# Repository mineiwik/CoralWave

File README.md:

# CoralWave

This repository contains the hardware design files for an RF transceiver system built using an ESP32-C3 module and a CC1101 RF chip. The communication between the ESP32-C3 and CC1101 is established through the Serial Peripheral Interface (SPI) protocol. The design is created using KiCad 7.

## Abstract

The project aims to create a versatile RF communication system by integrating the ESP32-C3 module and the CC1101 RF chip. The ESP32-C3 serves as the main controller, handling data processing and interfacing with external devices, while the CC1101 handles the RF communication with other compatible devices. This design allows for bi-directional communication over a designated RF frequency band, making it suitable for various applications such as replacing remote controls.

**Note:** The design around the CC1101 chip is tuned for the 315/433 MHz ISM/SRD frequency bands. (See the documentation of the [CC1101](https://www.ti.com/lit/ds/symlink/cc1101.pdf) chip for more information.)

## Opening the Design

Follow these steps to open the hardware design using KiCad 7:

1. Clone this repository to your local machine using the following command:

   ```
   git clone https://github.com/mineiwik/CoralWave.git
   ```

2. Launch KiCad 7.

3. Open the KiCad project by navigating to the project directory and locating the `.kicad_pro` file. This file stores the project information.

4. Once the project is open, you can access the schematic and PCB layout files by clicking on the respective buttons in the KiCad project manager.

5. Adjust the design and/or export the gerbel files for PCB production

## Design Files

The repository contains the following design files:

- Schematic files (`.kicad_sch`) - These files define the circuit connections and component values.
- PCB layout files (`.kicad_pcb`) - These files represent the physical arrangement of components on the PCB.
- Component libraries (see the `PCBLib` submodule) - Custom libraries that include footprints and symbols for the ESP32-C3, CC1101, and other components used in the design.

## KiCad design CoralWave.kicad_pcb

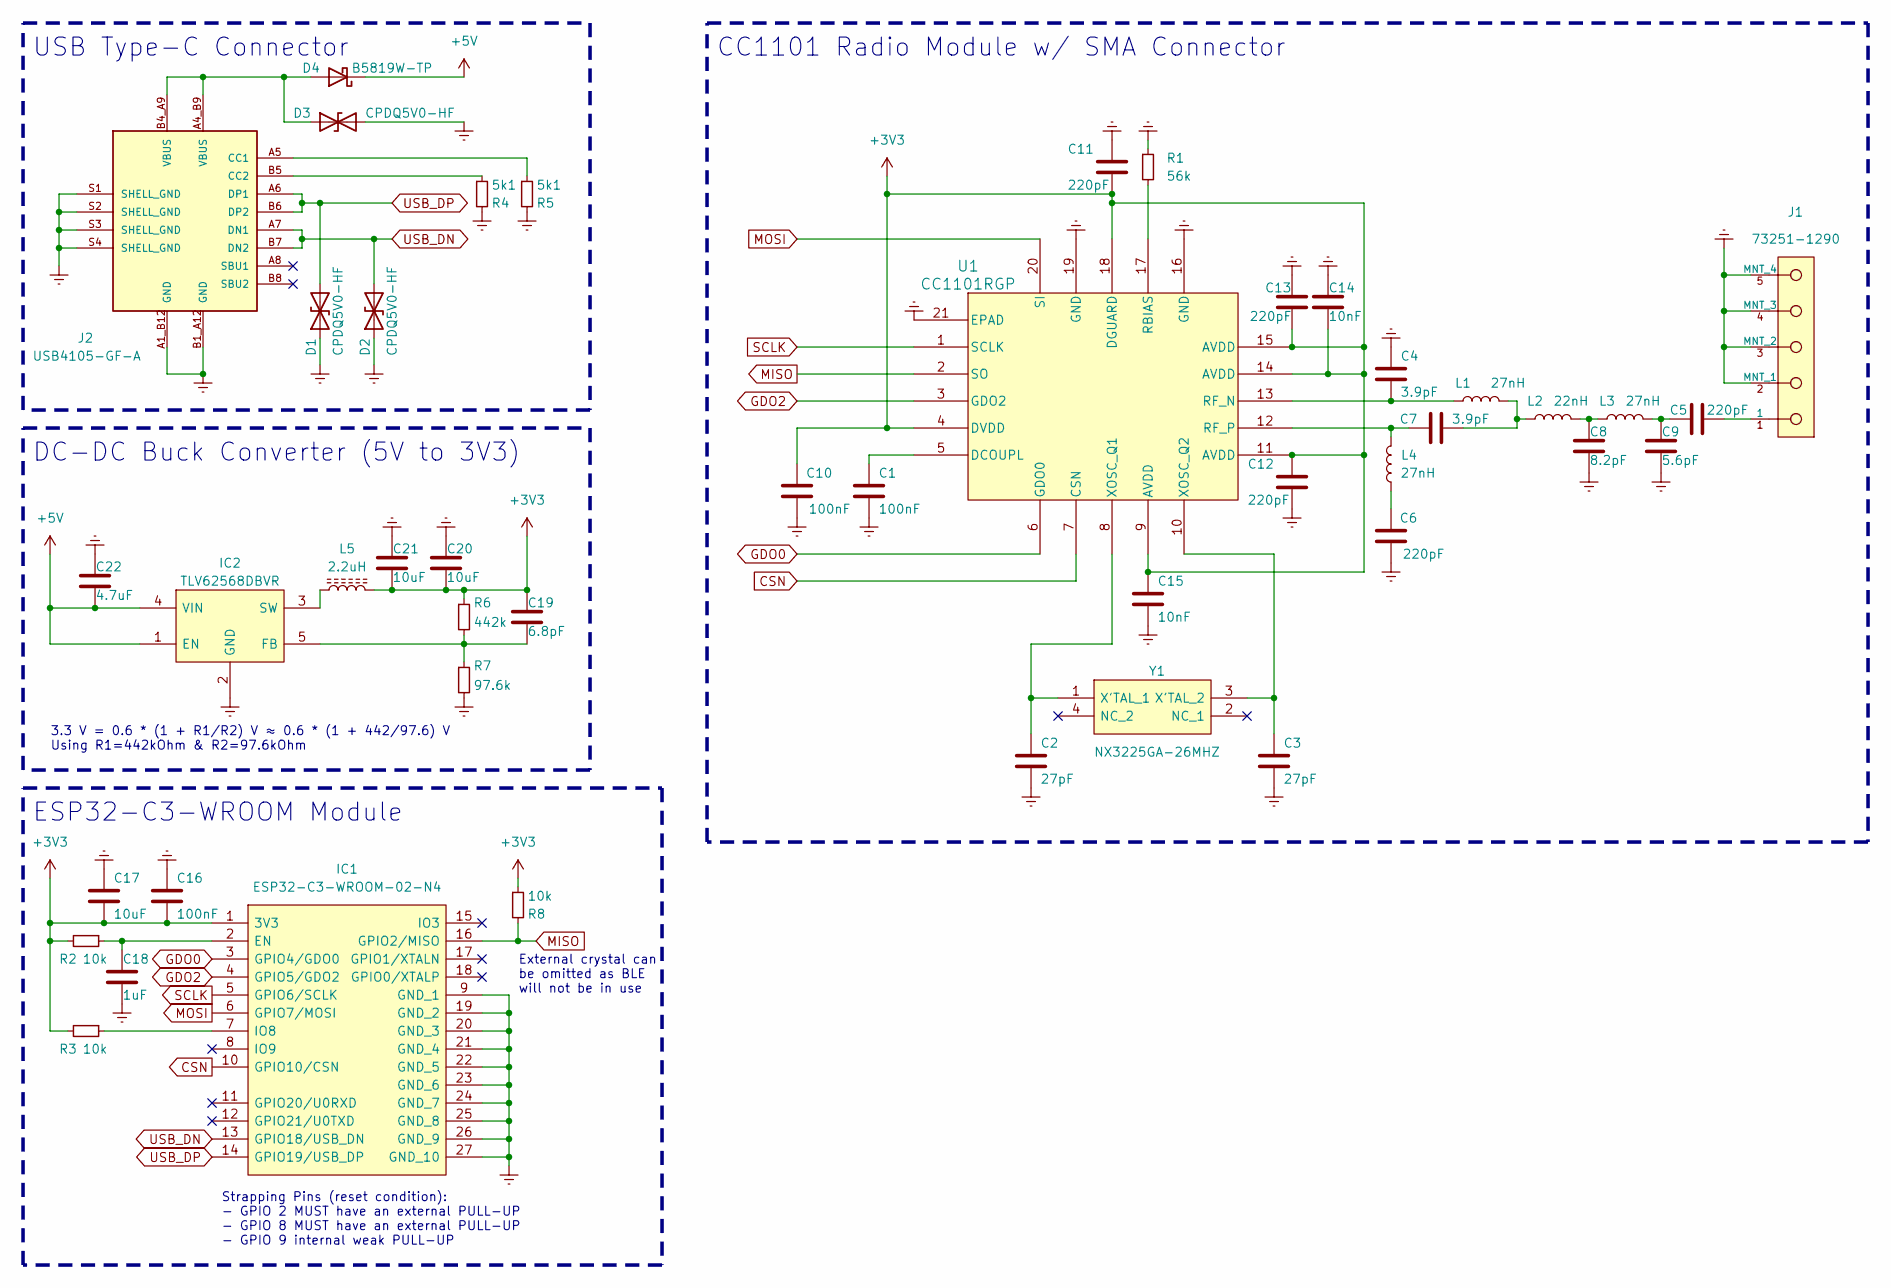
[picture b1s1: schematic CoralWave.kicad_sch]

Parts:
C1, C10, C16: 100nF; Cap_Murata_GRM_0402
C2, C3: 27pF; Cap_Murata_GRM_0402
C4, C7: 3.9pF; Cap_Murata_GRM_0402
C5, C6, C11, C12, C13: 220pF; Cap_Murata_GRM_0402
C8: 8.2pF; Cap_Murata_GRM_0402
C9: 5.6pF; Cap_Murata_GRM_0402
C14, C15: 10nF; Cap_Murata_GRM_0402
C17, C20, C21: 10uF; Cap_Murata_GRM_0402
C18: 1uF; Cap_Murata_GRM_0402
C19: 6.8pF; Cap_Murata_GRM_0402
C22: 4.7uF; Cap_Murata_GRM_0603
D1, D2, D3: CPDQ5V0-HF; SODFL1006X40N
D4: B5819W-TP; SOD3716X135N
IC1: ESP32-C3-WROOM-02-N4; ESP32C3WROOM02N4; Mouser Part Number 356-ESP32C3WROOM02N4
IC2: TLV62568DBVR; Mouser Part Number 595-TLV62568DBVR
J1: 73251-1290; Molex-SD-73251-129; mouser part number 538-73251-1290; digikey description SMA Connector Jack, Female Socket 50 Oh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
J2: USB4105-GF-A; GCT_USB4105-GF-A; PARTREV A3
L1, L3, L4: 27nH; L_Murata_LQG_0402
L2: 22nH; L_Murata_LQG_0402
L5: 2.2uH; ASPI0418FS
R1: 56k; R_KOA_RK_0402
R2, R3, R8: 10k; R_Vishay_CRCW_0402
R4, R5: 5k1; R_Vishay_CRCW_0402
R6: 442k; R_Bourns_CR_0603
R7: 97.6k; R_Bourns_CR_0603
U1: CC1101RGP
Y1: NX3225GA-26MHZ; NX3225GA16000MSTDCRG1; Mouser Part Number 344-NX3225GA26MHZEXS

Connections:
+3V3: C10.2, C11.2, C12.1, C13.2, C14.2, C15.1, C16.2, C17.2, C19.2, C20.2, C21.2, IC1.1 (3V3), L5.2, R2.2, R3.2, R6.1, R8.1, U1.4 (DVDD), U1.9 (AVDD), U1.11 (AVDD), U1.14 (AVDD), U1.15 (AVDD), U1.18 (DGUARD)
+5V: C22.1, D4.1 (K), IC2.1 (EN), IC2.4 (VIN)
CSN: IC1.10 (GPIO10/CSN), U1.7 (CSN)
Earth: C1.2, C2.2, C3.2, C4.1, C6.1, C8.1, C9.1, C10.1, C11.1, C12.2, C13.1, C14.1, C15.2, C16.1, C17.1, C18.2, C20.1, C21.1, C22.2, D1.1 (A1), D2.1 (A1), D3.2 (A2), IC1.9 (GND_1), IC1.19 (GND_2), IC1.20 (GND_3), IC1.21 (GND_4), IC1.22 (GND_5), IC1.23 (GND_6), IC1.24 (GND_7), IC1.25 (GND_8), IC1.26 (GND_9), IC1.27 (GND_10), IC2.2 (GND), J1.2 (MNT_1), J1.3 (MNT_2), J1.4 (MNT_3), J1.5 (MNT_4), J2.A1_B12 (GND), J2.B1_A12 (GND), J2.S1 (SHELL_GND), J2.S2 (SHELL_GND), J2.S3 (SHELL_GND), J2.S4 (SHELL_GND), R1.1, R4.2, R5.2, R7.2, U1.16 (GND), U1.19 (GND), U1.21 (EPAD)
GDO0: IC1.3 (GPIO4/GDO0), U1.6 (GDO0)
GDO2: IC1.4 (GPIO5/GDO2), U1.3 (GDO2)
MISO: IC1.16 (GPIO2/MISO), R8.2, U1.2 (SO)
MOSI: IC1.6 (GPIO7/MOSI), U1.20 (SI)
unnamed: C5.1, C9.2, L3.2
unnamed: C5.2, J1.1
unnamed: C6.2, L4.1
unnamed: C7.2, L1.2, L2.1
unnamed: C8.2, L2.2, L3.1
unnamed: D3.1 (A1), D4.2 (A), J2.A4_B9 (VBUS), J2.B4_A9 (VBUS)
unnamed: C18.1, IC1.2 (EN), R2.1
unnamed: IC1.7 (IO8), R3.1
unnamed: C19.1, IC2.5 (FB), R6.2, R7.1
unnamed: IC2.3 (SW), L5.1
unnamed: J2.A5 (CC1), R5.1
unnamed: J2.B5 (CC2), R4.1
unnamed: C1.1, U1.5 (DCOUPL)
unnamed: R1.2, U1.17 (RBIAS)
unnamed: C4.2, L1.1, U1.13 (RF_N)
unnamed: C7.1, L4.2, U1.12 (RF_P)
unnamed: C2.1, U1.8 (XOSC_Q1), Y1.1 (X'TAL_1)
unnamed: C3.1, U1.10 (XOSC_Q2), Y1.3 (X'TAL_2)
SCLK: IC1.5 (GPIO6/SCLK), U1.1 (SCLK)
USB_DN: D2.2 (A2), IC1.13 (GPIO18/USB_DN), J2.A7 (DN1), J2.B7 (DN2)
USB_DP: D1.2 (A2), IC1.14 (GPIO19/USB_DP), J2.A6 (DP1), J2.B6 (DP2)

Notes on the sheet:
Strapping Pins (reset condition): - GPIO 2 MUST have an external PULL-UP - GPIO 8 MUST have an external PULL-UP - GPIO 9 internal weak PULL-UP
CC1101 Radio Module w/ SMA Connector
3.3 V = 0.6 * (1 + R1/R2) V ≈ 0.6 * (1 + 442/97.6) V Using R1=442kOhm & R2=97.6kOhm
DC-DC Buck Converter (5V to 3V3)
ESP32-C3-WROOM Module
External crystal can be omitted as BLE will not be in use
USB Type-C Connector

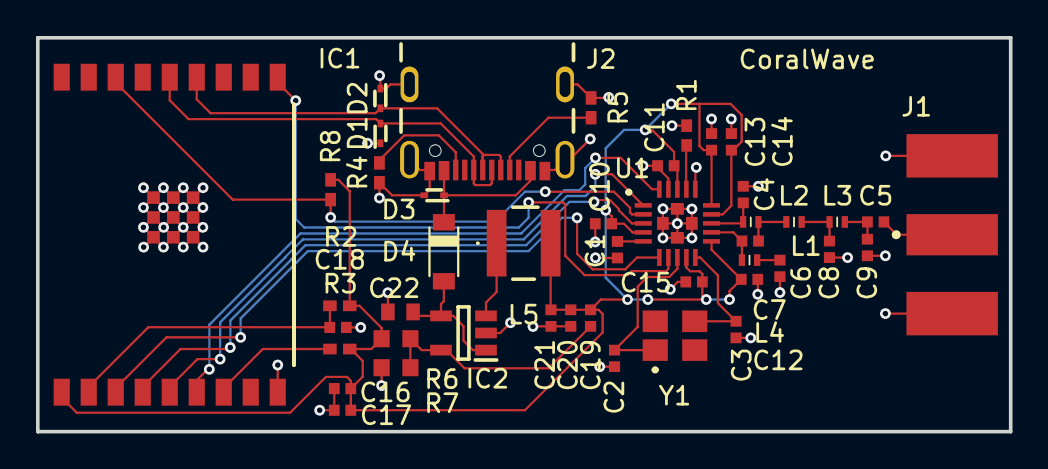
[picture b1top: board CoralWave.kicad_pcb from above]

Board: 2 copper layers, 54.0 x 21.9 mm, 45 parts (0 on the bottom side), 29 nets.

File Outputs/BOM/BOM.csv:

Id,Designator,Footprint,Quantity,Designation,Manufacturer Nr.,Mouser Nr.
1,Y1,NX3225GA16000MSTDCRG1,1,NX3225GA-26MHZ,NX3225GA-26.000MHZ-EXS00A-CG01972,344-NX3225GA26MHZEXS
2,"C16,C1,C10",Cap_Murata_GRM_0402,3,100nF,GRM155C71H104JE19J,81-GRM155C71H104JE9J
3,"C2,C3",Cap_Murata_GRM_0402,2,27pF,GRM1555C1H270JA01D,81-GRM1555C1H270JA1D
4,"C5,C6,C13,C11,C12",Cap_Murata_GRM_0402,5,220pF,GRM1555C1H221JA01J,81-GRM1555C1H221JA1J
5,U1,CC1101RGP,1,CC1101RGP,CC1101RGPR,595-CC1101RGPR
6,R6,R_Bourns_CR_0603,1,442k,CR0603-FX-4423ELF,652-CR0603FX4423ELF
7,C19,Cap_Murata_GRM_0402,1,6.8pF,GRM1555C1E6R8BA01D,81-GRM1555C1E6R8BA1D
8,"R8,R2,R3",R_Vishay_CRCW_0402,3,10k,CRCW040210K0FKEDC,71-CRCW040210K0FKEDC
9,C22,Cap_Murata_GRM_0603,1,4.7uF,GRM188R61C475KE11D,81-GRM188R61C475KE1D
10,R7,R_Bourns_CR_0603,1,97.6k,CR0603-FX-9762ELF,652-CR0603FX-9762ELF
11,"L3,L4,L1",L_Murata_LQG_0402,3,27nH,LQG15HS27NJ02D,81-LQG15HS27NJ02D
12,"C20,C17,C21",Cap_Murata_GRM_0402,3,10uF,GRM155R61A106ME11D,81-GRM155R61A106ME1D
13,D4,SOD3716X135N,1,B5819W-TP,B5819W-TP,833-B5819W-TP
14,"D3,D2,D1",SODFL1006X40N,3,CPDQ5V0-HF,CPDQ5V0-HF,750-CPDQ5V0-HF
15,R1,R_KOA_RK_0402,1,56k,RK73H1ETTP5602F,660-RK73H1ETTP5602F
16,J1,Molex-SD-73251-129,1,73251-1290,73251-1290,538-73251-1290
17,"R4,R5",R_Vishay_CRCW_0402,2,5k1,CRCW04025K10FKEDC,71-CRCW04025K10FKEDC
18,"C7,C4",Cap_Murata_GRM_0402,2,3.9pF,GRM1555C1H3R9CA01D,81-GRM1555C1H3R9CA1D
19,J2,GCT_USB4105-GF-A,1,USB4105-GF-A,USB4105-GF-A,640-USB4105-GF-A
20,IC1,ESP32C3WROOM02N4,1,ESP32-C3-WROOM-02-N4,ESP32-C3-WROOM-02-N4,356-ESP32C3WROOM02N4
21,C8,Cap_Murata_GRM_0402,1,8.2pF,GRM1555C1H8R2BA01D,81-GRM1555C1H8R2BA1D
22,C18,Cap_Murata_GRM_0402,1,1uF,GRM155C81A105KA12J,81-GRM155C81A105KA2J
23,C9,Cap_Murata_GRM_0402,1,5.6pF,GRM1555C1E5R6CA01D,81-GRM1555C1E5R6CA1D
24,"C15,C14",Cap_Murata_GRM_0402,2,10nF,GRM155R71E103KA01D,81-GRM36X103K25
25,L2,L_Murata_LQG_0402,1,22nH,LQG15HS22NJ02D,81-LQG15HS22NJ02D
26,L5,ASPI0418FS,1,2.2uH,ASPI-0418FS-2R2M-T3,815-ASPI418FS2R2MT3
27,IC2,TLV62568DBVR,1,TLV62568DBVR,TLV62568DBVR,595-TLV62568DBVR

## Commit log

2023-08-22 Add BOM
2023-08-22 Regenerate fab files
